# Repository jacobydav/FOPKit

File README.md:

# FOPKit
Fiber Optic Painting Kit

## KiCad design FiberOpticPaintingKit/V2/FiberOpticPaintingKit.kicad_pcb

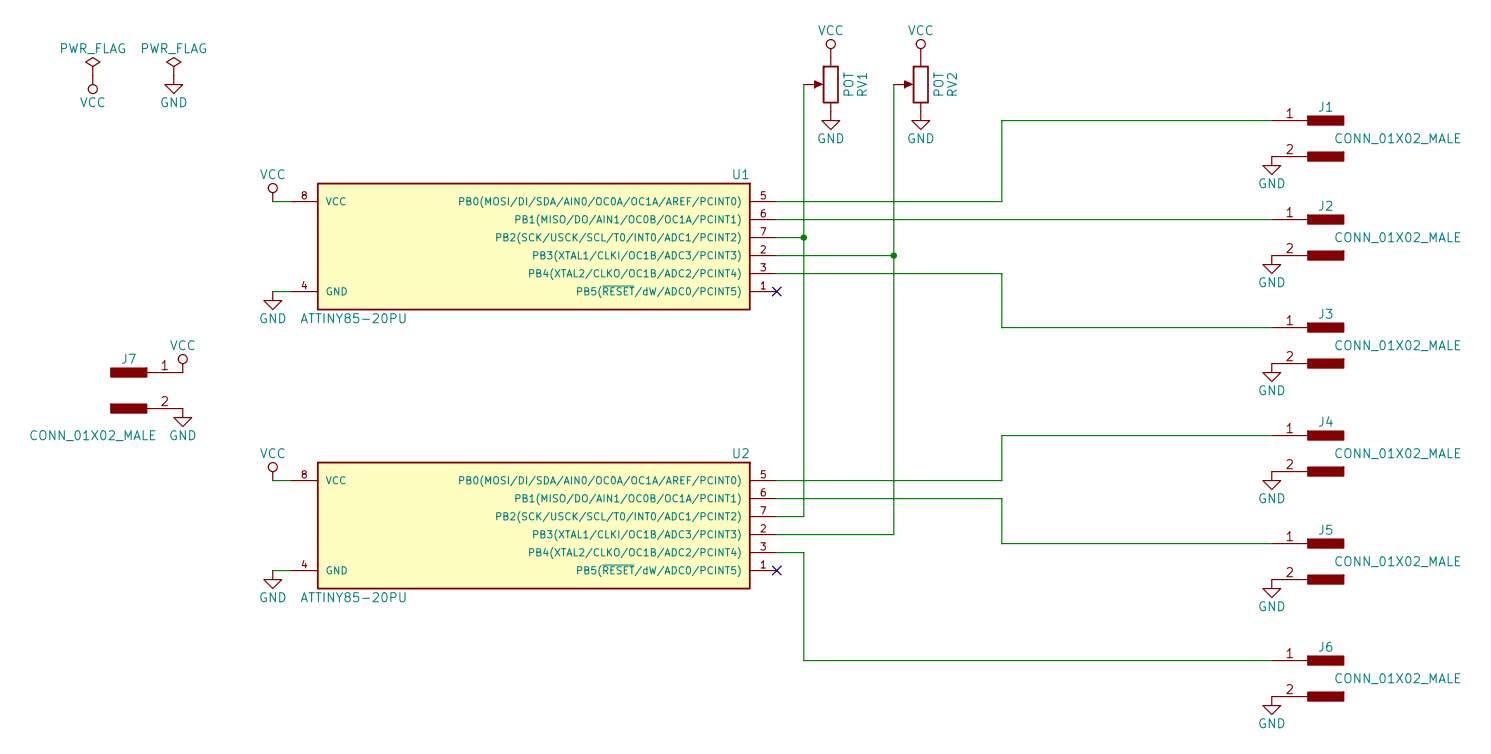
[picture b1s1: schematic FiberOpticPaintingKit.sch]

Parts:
J1, J2, J3, J4, J5, J6, J7: CONN_01X02_MALE; Pin_Header_Straight_1x02_Pitch2.00mm
RV1, RV2: POT; Potentiometer_Trimmer_VishaySpectrol_Econtrim-Type36T
U1, U2: ATTINY85-20PU; DIP-8_W7.62mm

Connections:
GND: J1.2, J2.2, J3.2, J4.2, J5.2, J6.2, J7.2, RV1.3, RV2.3, U1.4 (GND), U2.4 (GND)
unnamed: J1.1, U1.5 (PB0(MOSI/DI/SDA/AIN0/OC0A/OC1A/AREF/PCI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)
unnamed: J2.1, U1.6 (PB1(MISO/DO/AIN1/OC0B/OC1A/PCINT1))
unnamed: J3.1, U1.3 (PB4(XTAL2/CLKO/OC1B/ADC2/PCINT4))
unnamed: J4.1, U2.5 (PB0(MOSI/DI/SDA/AIN0/OC0A/OC1A/AREF/PCI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)
unnamed: J5.1, U2.6 (PB1(MISO/DO/AIN1/OC0B/OC1A/PCINT1))
unnamed: J6.1, U2.3 (PB4(XTAL2/CLKO/OC1B/ADC2/PCINT4))
unnamed: RV1.2, U1.7 (PB2(SCK/USCK/SCL/T0/INT0/ADC1/PCINT2)), U2.7 (PB2(SCK/USCK/SCL/T0/INT0/ADC1/PCINT2))
unnamed: RV2.2, U1.2 (PB3(XTAL1/CLKI/OC1B/ADC3/PCINT3)), U2.2 (PB3(XTAL1/CLKI/OC1B/ADC3/PCINT3))
VCC: J7.1, RV1.1, RV2.1, U1.8 (VCC), U2.8 (VCC)

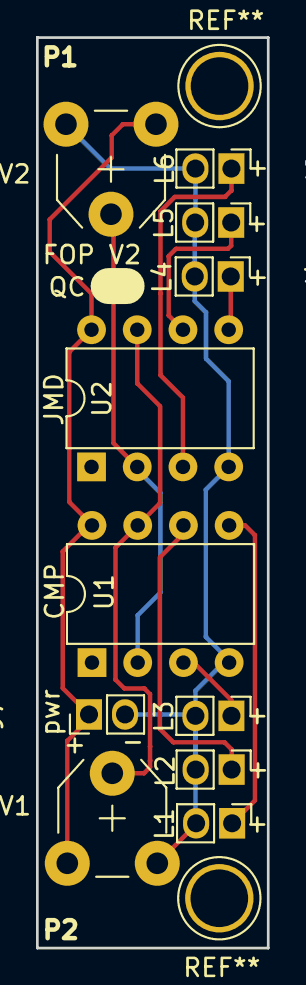
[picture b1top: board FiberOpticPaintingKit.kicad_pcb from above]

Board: 2 copper layers, 12.8 x 50.6 mm, 11 parts (0 on the bottom side), 10 nets.

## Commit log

2018-05-20 Initial add of files
2019-11-02 PCB assembly instructions
    Added PCB assembly instructions
